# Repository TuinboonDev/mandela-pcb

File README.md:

# Mandela

A single PCB thats 1/5th of a larger circle with each part lighting up an LED and one part being controlled by a potentiometer.

## Schematic

## PCB

## 3D

## BOM
- 1   Potentiometer
- 5   Resistors
- 1   Battery holder
- 5   LED

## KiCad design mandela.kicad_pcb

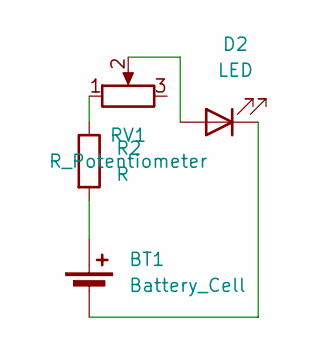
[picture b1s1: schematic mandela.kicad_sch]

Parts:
BT1: Battery_Cell; BatteryHolder_Keystone_3034_1x20mm MODIFIED
D2: LED; LED_D5.0mm
R2: R; R_Axial_DIN0207_L6.3mm_D2.5mm_P7.62mm_Horizontal
RV1: R_Potentiometer; Potentiometer_Vishay_T73YP_Vertical

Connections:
unnamed: BT1.1 (+), R2.2
unnamed: BT1.2 (-), D2.1 (K)
unnamed: D2.2 (A), RV1.2
unnamed: R2.1, RV1.1

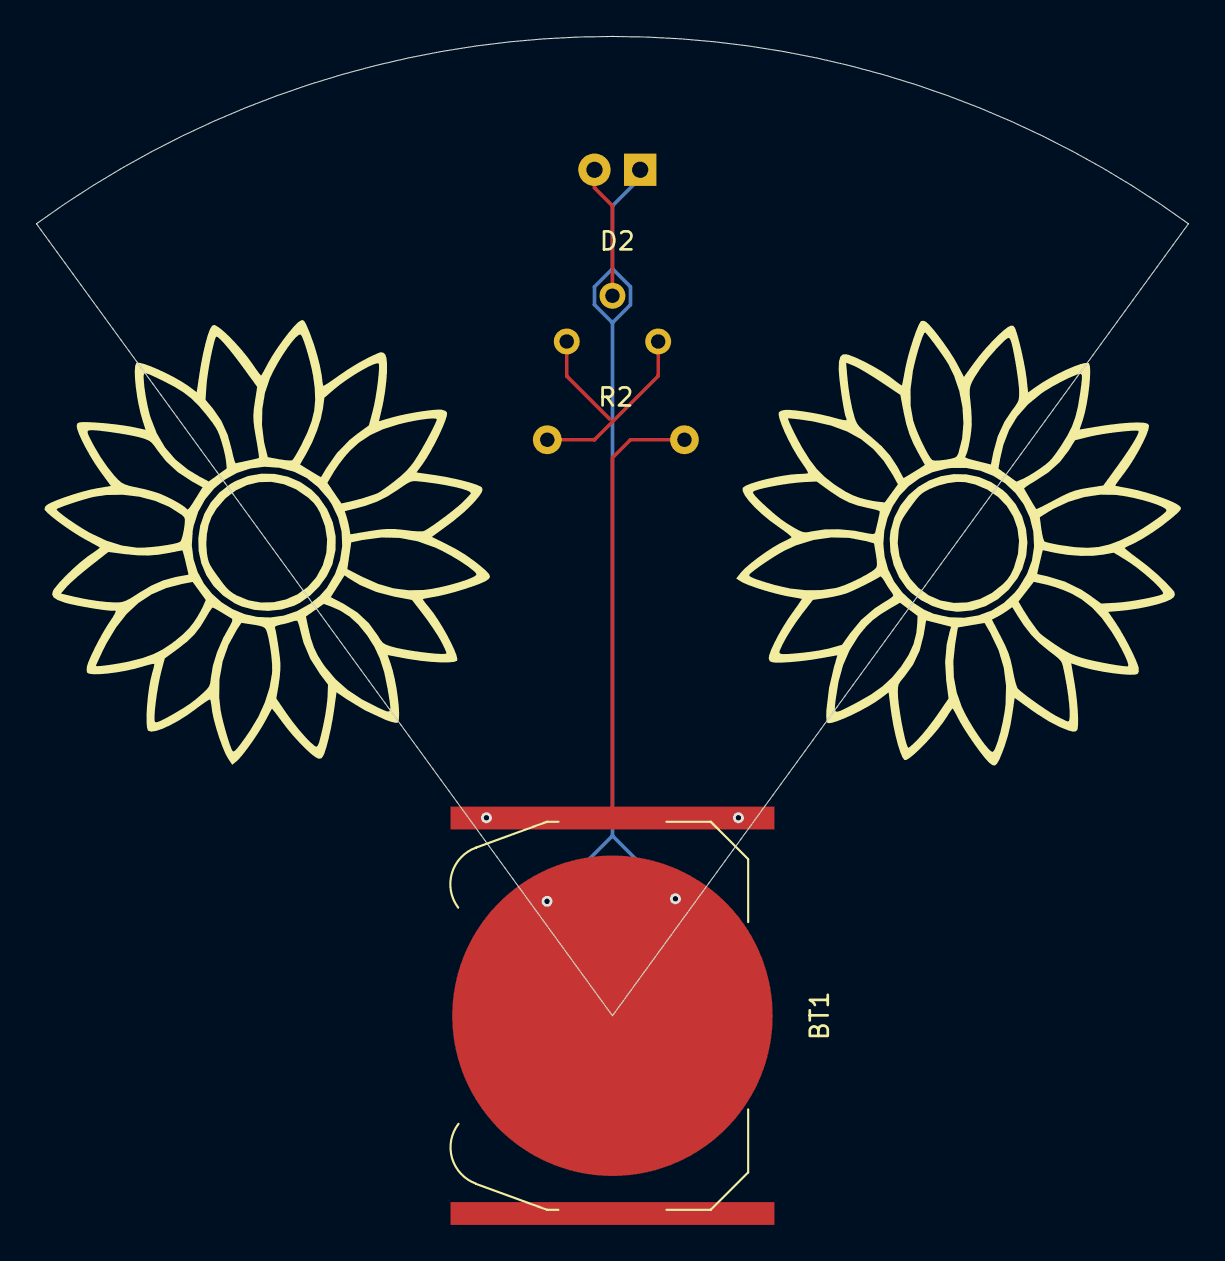
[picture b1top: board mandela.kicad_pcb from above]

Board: 2 copper layers, 64.0 x 54.4 mm, 4 parts (0 on the bottom side), 4 nets.

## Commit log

2025-06-26 Upload PCB files
2025-06-26 Upload gerber
2025-06-26 Create test
2025-06-28 Update files
